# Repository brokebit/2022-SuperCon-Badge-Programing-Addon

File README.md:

# 2022 SuperCon Badge USB Programing Add On Module
This project is an open-source hardware add-on that allows you to easily upload & download programs via USB and interact with the Input & Output pins via buttons and LEDs. It also passes all header pins through so you can daisy chain other add-ons. Input buttons, output LEDs, and USB UART can all be disabled via DIP switches. 

The board is a 6-layer design made in KiCad. The surface mount parts should be available directly from JLC PCB, and the through-hole parts are available via Digiki or your other favorite supplier. 

The 5V USB supply only powers the USB UART. 

## Through Hole Parts
- [12 Pin Femaile Header](https://www.digikey.com/en/products/detail/sullins-connector-solutions/PPTC121LGBN-RC/775906)
- [12 Pin Male Header](https://www.digikey.com/en/products/detail/adam-tech/PH1RA-12-UA/9830541)
- [4 Position SPST DIP Switch 2.54mm pitch](https://www.digikey.com/en/products/detail/grayhill-inc/76SB04T/726228)
- [2 Position SPST DIP Switch 2.54mm pitch](https://www.digikey.com/en/products/detail/grayhill-inc/76SB02ST/726171)
- [6mm Buttons](https://www.digikey.com/en/products/detail/te-connectivity-alcoswitch-switches/1825910-3/2400476)
## Features
- Passthrough header
- Four input buttons for input I/O pins
- Four output LEDs for output I/O pins
- CP210x USB Uart for serial I/O and upload/download programs
## Resources
- [Schematic](https://github.com/brokebit/2022-SuperCon-Badge-Programing-Addon/blob/main/Schematic-111222-v0.1.pdf?raw=true)
- [BOM file for PCB Manufacturer](https://github.com/brokebit/2022-SuperCon-Badge-Programing-Addon/blob/main/Manufacturing/BOM_ProgramingAddOn.xlsx?raw=true)
- [Position file for PCB Manufacturer](https://github.com/brokebit/2022-SuperCon-Badge-Programing-Addon/blob/main/Manufacturing/ProgramingAddOn-pos.xlsx?raw=true)
- [Gerber files for PCB Manufacturer](https://github.com/brokebit/2022-SuperCon-Badge-Programing-Addon/blob/main/Manufacturing/ProgramingAddOn.zip?raw=true)

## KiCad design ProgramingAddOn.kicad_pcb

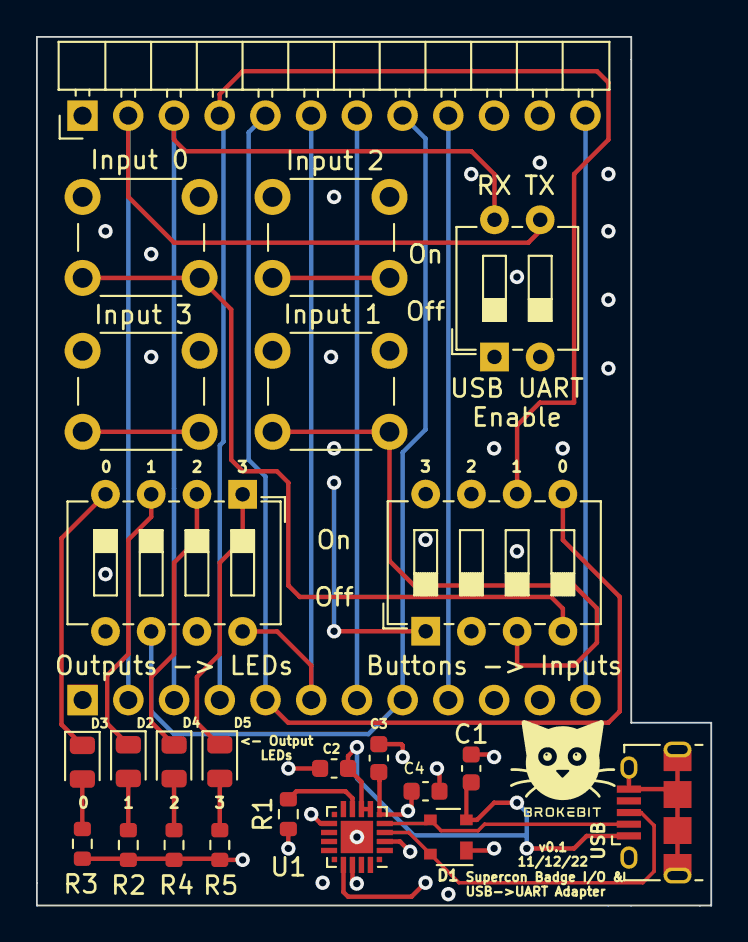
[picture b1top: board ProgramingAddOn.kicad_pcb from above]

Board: 6 copper layers, 37.5 x 48.3 mm, 25 parts (1 on the bottom side), 29 nets.

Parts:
C1, C2, C3, C4: C; C_0603_1608Metric
D1: SP0503BAHT; SOT-143
D2, D3, D4, D5: LED; LED_0805_2012Metric
J1: USB_B_Micro; USB_Micro-B_Amphenol_10118194_Horizontal
J4: Conn_01x12_Male; PinHeader_1x12_P2.54mm_Horizontal
J5: Conn_01x12_Female; PinHeader_1x12_P2.54mm_Horizontal
R1, R2, R3, R4, R5: R_US; R_0603_1608Metric
SW1: SW_DIP_x02; SW_DIP_SPSTx02_Slide_6.7x6.64mm_W7.62mm_P2.54mm_LowProfile
SW2, SW3, SW4, SW6: SW_Push; SW_PUSH_6mm
SW5, SW7: SW_DIP_x04; SW_DIP_SPSTx04_Slide_6.7x11.72mm_W7.62mm_P2.54mm_LowProfile
U1: CP2102N-Axx-xQFN20; SiliconLabs_QFN-20-1EP_3x3mm_P0.5mm_EP1.8x1.8mm

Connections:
+3.3V: C3.1, C4.1, J4.11, J5.11, R1.1, SW2.1, SW3.1, SW4.1, SW6.1, U1.6 (VDD)
/D+: D1.4 (K), J1.3 (D+), U1.4 (D+)
/D-: D1.3 (K), J1.2 (D-), U1.5 (D-)
/In-0: J4.5, J5.5, SW7.5
/In-1: J4.4, J5.4, SW7.6
/In-2 / RX: J4.3, J5.3, SW1.4, SW7.7
/In-3 / TX: J4.2, J5.2, SW1.3, SW7.8
/Out-0: J4.9, J5.9, SW5.5
/Out-1: J4.8, J5.8, SW5.6
/Out-2: J4.7, J5.7, SW5.7
/Out-3: J4.6, J5.6, SW5.8
/RXD: SW1.2, U1.17 (RXD)
/Reset: J4.12, J5.12
/TXD: SW1.1, U1.18 (TXD)
GND: C1.2, C2.2, C3.2, C4.2, D1.1 (A), J1.5 (GND), J1.6 (Shield), J4.1, J4.10, J5.1, J5.10, R2.1, R3.1, R4.1, R5.1, U1.3 (GND), U1.12 (GND), U1.21 (GND)
unnamed: D2.1 (K), SW5.3
unnamed: D2.2 (A), R2.2
unnamed: D3.1 (K), SW5.4
unnamed: D3.2 (A), R3.2
unnamed: D4.1 (K), SW5.2
unnamed: D4.2 (A), R4.2
unnamed: D5.1 (K), SW5.1
unnamed: D5.2 (A), R5.2
unnamed: R1.2, U1.9 (~RST)
unnamed: SW2.2, SW7.2
unnamed: SW3.2, SW7.4
unnamed: SW4.2, SW7.1
unnamed: SW6.2, SW7.3
VBUS: C1.1, C2.1, D1.2 (K), J1.1 (VBUS), U1.7 (VREGIN), U1.8 (VBUS)

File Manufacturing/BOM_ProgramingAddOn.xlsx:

Ref | Qnty | Value | Cmp name | Footprint | Description | Vendor
C1, C4, | 2 | .1uf | C | Capacitor_SMD:C_0603_1608Metric | Unpolarized capacitor
C2, C3, | 2 | 4.7uf | C | Capacitor_SMD:C_0603_1608Metric | Unpolarized capacitor
D1, | 1 | SP0503BAHT | SP0503BAHT | Package_TO_SOT_SMD:SOT-143 | TVS Diode Array, 5.5V Standoff, 3 Channels, SOT-143 package
D2, D3, D4, D5, | 4 | 50 Ohms | LED | LED_SMD:LED_0805_2012Metric | Light emitting diode
J1, | 1 | USB_B_Micro | USB_B_Micro | Connector_USB:USB_Micro-B_Amphenol_10118194_Horizontal | USB Micro Type B connector
J4, | 1 | Conn_01x12_Male | Conn_01x12_Male | Connector_PinHeader_2.54mm:PinHeader_1x12_P2.54mm_Horizontal | Generic connector, single row, 01x12, script generated (kicad-library-utils/sch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
J5, | 1 | Conn_01x12_Female | Conn_01x12_Female | Connector_PinHeader_2.54mm:PinHeader_1x12_P2.54mm_Horizontal | Generic connector, single row, 01x12, script generated (kicad-library-utils/sch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
R1, | 1 | 1k | R_US | Resistor_SMD:R_0603_1608Metric | Resistor, US symbol
R2, R3, R4, R5, | 4 | R_US | R_US | Resistor_SMD:R_0603_1608Metric | Resistor, US symbol
SW1, | 1 | SW_DIP_x02 | SW_DIP_x02 | Button_Switch_THT:SW_DIP_SPSTx02_Slide_6.7x6.64mm_W7.62mm_P2.54mm_LowProfile | 2x DIP Switch, Single Pole Single Throw (SPST) switch, small symbol
SW2, SW3, SW4, SW6, | 4 | SW_Push | SW_Push | Button_Switch_THT:SW_PUSH_6mm | Push button switch, generic, two pins
SW5, SW7, | 2 | SW_DIP_x04 | SW_DIP_x04 | Button_Switch_THT:SW_DIP_SPSTx04_Slide_6.7x11.72mm_W7.62mm_P2.54mm_LowProfile | 4x DIP Switch, Single Pole Single Throw (SPST) switch, small symbol
U1, | 1 | CP2102N-Axx-xQFN20 | CP2102N-Axx-xQFN20 | Package_DFN_QFN:SiliconLabs_QFN-20-1EP_3x3mm_P0.5mm_EP1.8x1.8mm | USB to UART master bridge, QFN-20

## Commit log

2022-12-05 Add schematic PDF and PCB rendering
2022-12-05 Add image to README.md
2022-12-05 Add image of actual device on badge
2022-12-05 Add rendering of back
2022-12-06 Clean up README
2022-12-11 Update part descriptions. Change USB mini to micro.
2022-12-11 Rename git ignore file
